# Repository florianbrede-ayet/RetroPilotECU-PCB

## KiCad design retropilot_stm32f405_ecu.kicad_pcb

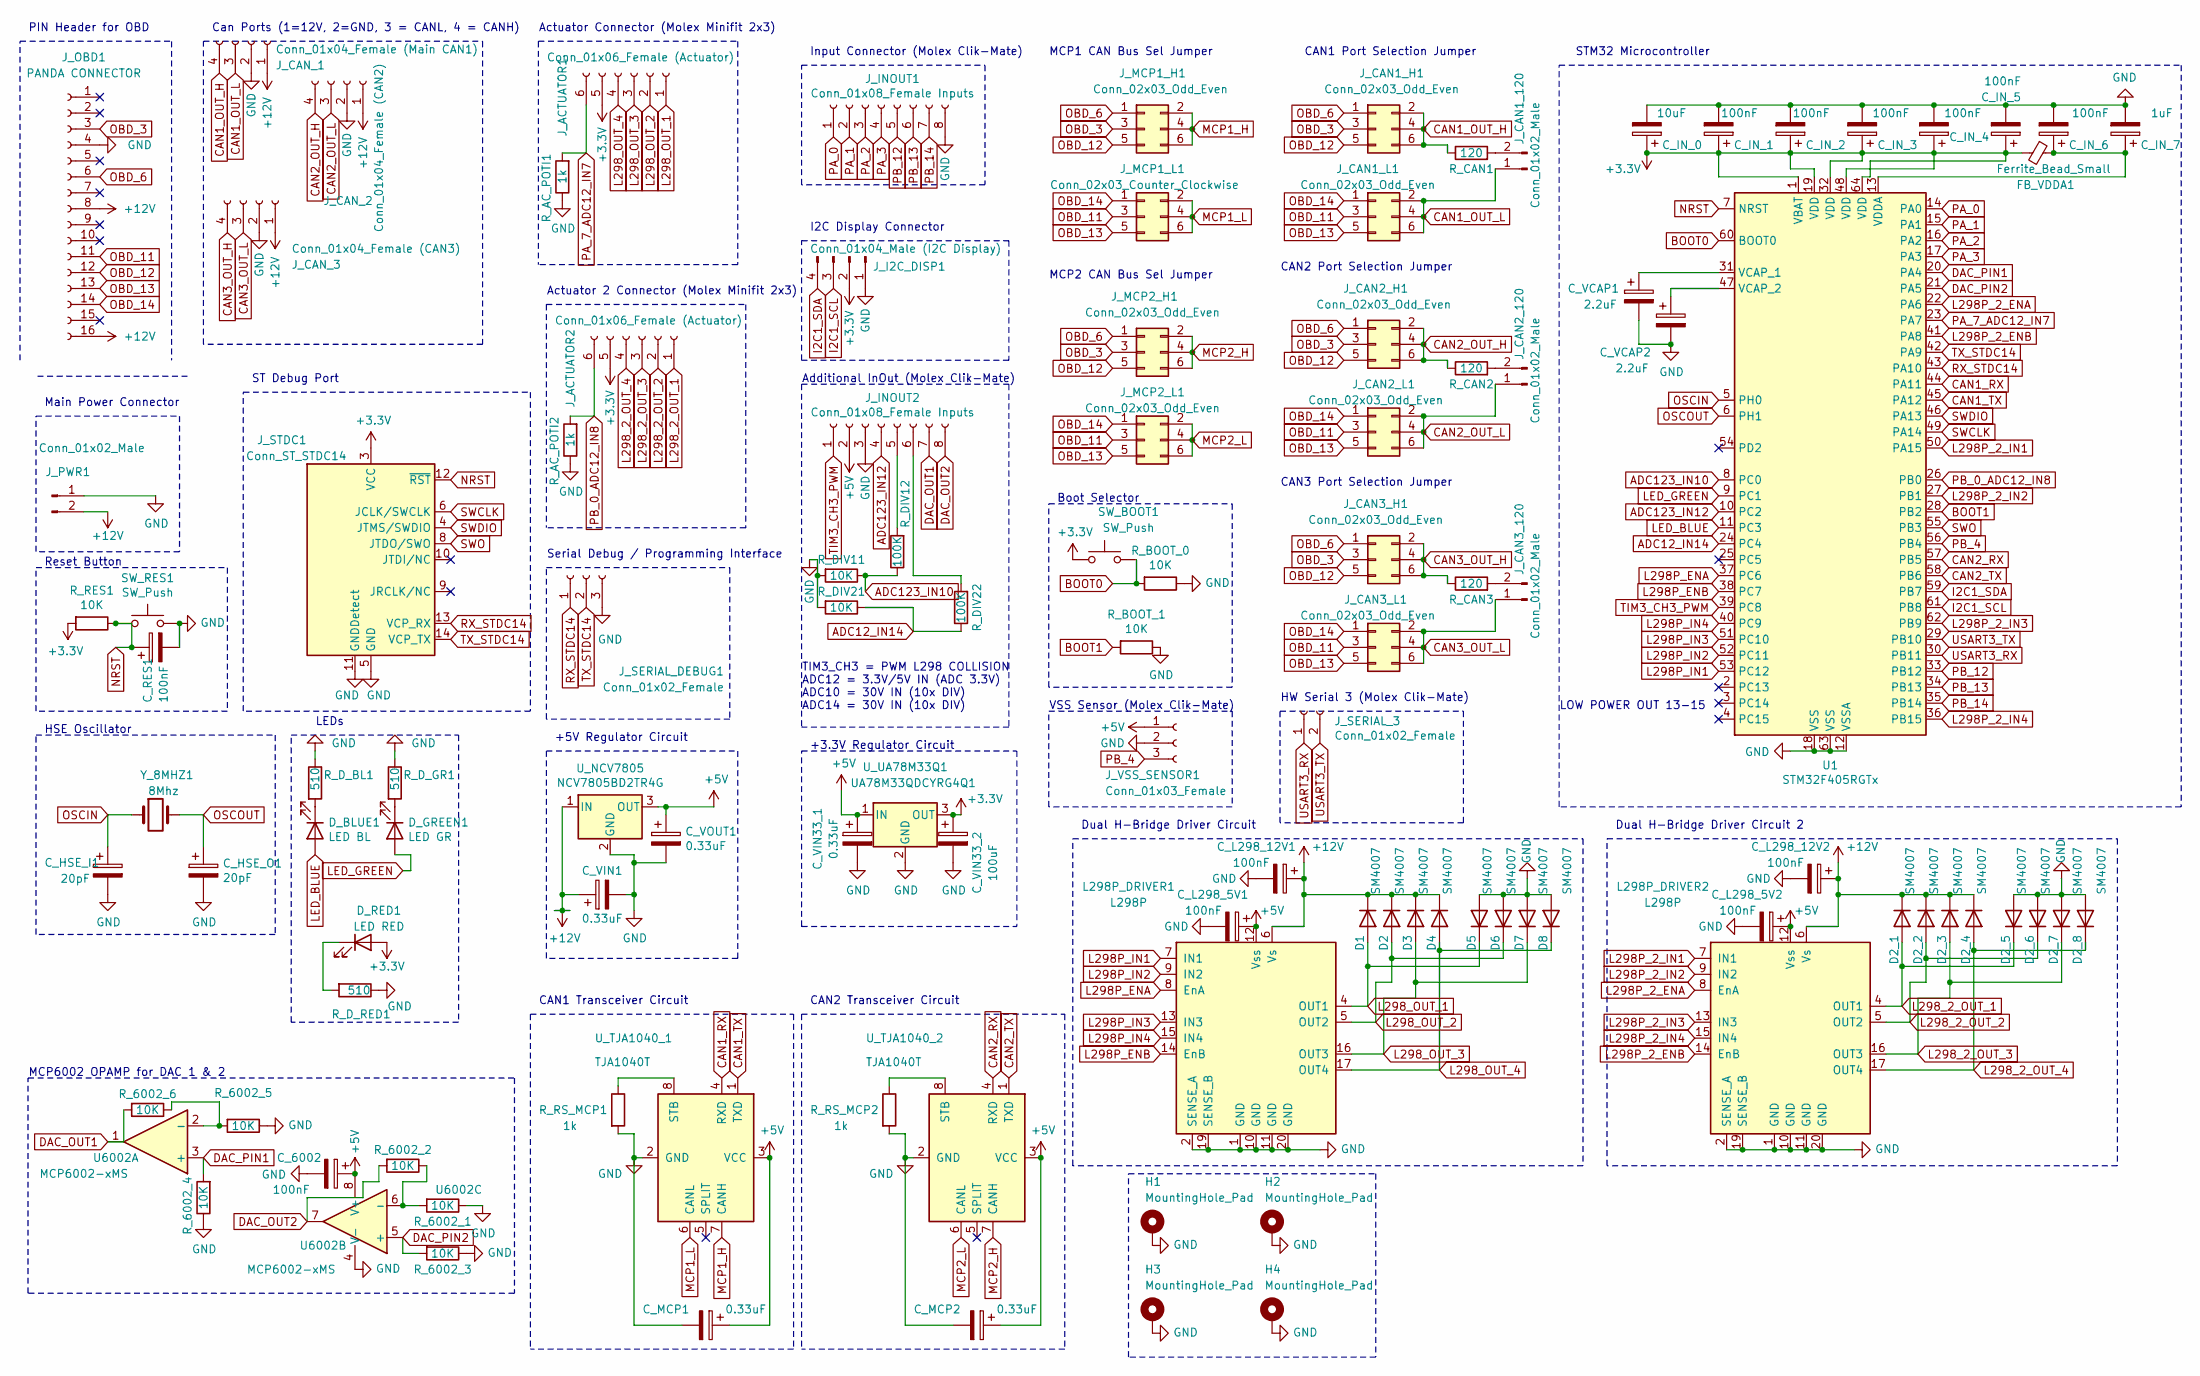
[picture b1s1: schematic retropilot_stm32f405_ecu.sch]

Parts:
C_6002: 100nF; C_0402_1005Metric
C_HSE_I1: 20pF; C_0603_1608Metric
C_HSE_O1: 20pF; C_0603_1608Metric
C_IN_0: 10uF; CP_EIA-3216-18_Kemet-A
C_IN_1, C_IN_2, C_IN_3, C_IN_4, C_IN_5, C_IN_6: 100nF; C_0402_1005Metric
C_IN_7: 1uF; C_1206_3216Metric
C_L298_5V1, C_L298_5V2, C_L298_12V1, C_L298_12V2: 100nF; C_0402_1005Metric
C_MCP1, C_MCP2: 0.33uF; C_0805_2012Metric
C_RES1: 100nF; C_0402_1005Metric
C_VCAP1, C_VCAP2: 2.2uF; C_1206_3216Metric
C_VIN1, C_VIN33_1: 0.33uF; C_0805_2012Metric
C_VIN33_2: 100uF; CP_EIA-3528-15_AVX-H
C_VOUT1: 0.33uF; C_0805_2012Metric
D1, D2, D2_1, D2_2, D2_3, D2_4, D2_5, D2_6, D2_7, D2_8, D3, D4, D5, D6, D7, D8: SM4007; D_SOD-123F
D_BLUE1: LED BL; LED_0603_1608Metric
D_GREEN1: LED GR; LED_0603_1608Metric
D_RED1: LED RED; LED_0603_1608Metric
FB_VDDA1: Ferrite_Bead_Small; R_0805_2012Metric
H1, H2, H3, H4: MountingHole_Pad; MountingHole_3.2mm_M3_DIN965_Pad
J_ACTUATOR1, J_ACTUATOR2: Conn_01x06_Female (Actuator); Molex_Mini-Fit_Jr_5569-06A2_2x03_P4.20mm_Horizontal
J_CAN1_120, J_CAN2_120, J_CAN3_120: Conn_01x02_Male; PinHeader_1x02_P1.27mm_Vertical
J_CAN1_H1, J_CAN1_L1, J_CAN2_H1, J_CAN2_L1, J_CAN3_H1, J_CAN3_L1: Conn_02x03_Odd_Even; PinHeader_2x03_P1.27mm_Vertical
J_CAN_1: Conn_01x04_Female (Main CAN1); Molex_Mini-Fit_Jr_5569-04A2_2x02_P4.20mm_Horizontal
J_CAN_2: Conn_01x04_Female (CAN2); Molex_Mini-Fit_Jr_5569-04A2_2x02_P4.20mm_Horizontal
J_CAN_3: Conn_01x04_Female (CAN3); Molex_Mini-Fit_Jr_5569-04A2_2x02_P4.20mm_Horizontal
J_I2C_DISP1: Conn_01x04_Male (I2C Display); PinSocket_1x04_P2.54mm_Vertical
J_INOUT1, J_INOUT2: Conn_01x08_Female Inputs; Molex_CLIK-Mate_502386-0870_1x08-1MP_P1.25mm_Horizontal
J_MCP1_H1, J_MCP2_H1, J_MCP2_L1: Conn_02x03_Odd_Even; PinHeader_2x03_P1.27mm_Vertical
J_MCP1_L1: Conn_02x03_Counter_Clockwise; PinHeader_2x03_P1.27mm_Vertical
J_OBD1: PANDA CONNECTOR; C-OBD-II-16M-E-N-12V
J_PWR1: Conn_01x02_Male; Molex_Mini-Fit_Jr_5569-02A2_2x01_P4.20mm_Horizontal
J_SERIAL_3: Conn_01x02_Female; Molex_CLIK-Mate_502386-0270_1x02-1MP_P1.25mm_Horizontal
J_SERIAL_DEBUG1: Conn_01x02_Female; PinSocket_1x03_P2.54mm_Horizontal
J_STDC1: Conn_ST_STDC14; PinHeader_2x07_P2.54mm_Vertical
J_VSS_SENSOR1: Conn_01x03_Female; Molex_CLIK-Mate_502386-0370_1x03-1MP_P1.25mm_Horizontal
L298P_DRIVER1, L298P_DRIVER2: L298P; HSOP-20-1EP_11.0x15.9mm_P1.27mm_SlugDown
R_6002_1, R_6002_2, R_6002_3, R_6002_4, R_6002_5, R_6002_6: 10K; R_0603_1608Metric
R_AC_POTI1, R_AC_POTI2: 1k; R_0603_1608Metric
R_BOOT_0, R_BOOT_1: 10K; R_0603_1608Metric
R_CAN1, R_CAN2, R_CAN3: 120; R_0603_1608Metric
R_DIV11, R_DIV21: 10K; R_0603_1608Metric
R_DIV12, R_DIV22: 100K; R_0603_1608Metric
R_D_BL1: 510; R_0603_1608Metric
R_D_GR1: 510; R_0603_1608Metric
R_D_RED1: 510; R_0603_1608Metric
R_RES1: 10K; R_0603_1608Metric
R_RS_MCP1, R_RS_MCP2: 1k; R_0603_1608Metric
SW_BOOT1: SW_Push; SW_Push_1P1T_NO_CK_KSC6xxJ
SW_RES1: SW_Push; SW_Push_1P1T_NO_CK_KSC6xxJ
U1: STM32F405RGTx; LQFP-64_10x10mm_P0.5mm
U6002: MCP6002-xMS; SOIC-8_3.9x4.9mm_P1.27mm
U_NCV7805: NCV7805BD2TR4G; TO-263-3_TabPin2
U_TJA1040_1, U_TJA1040_2: TJA1040T; SOIC-8_3.9x4.9mm_P1.27mm
U_UA78M33Q1: UA78M33QDCYRG4Q1; SOT-223-3_TabPin2
Y_8MHZ1: 8Mhz; Crystal_SMD_5032-2Pin_5.0x3.2mm

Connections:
+3V3: C_IN_0.1, C_IN_1.1, C_IN_2.1, C_IN_3.1, C_IN_4.1, C_IN_5.1, C_VIN33_2.1, D_RED1.2 (A), FB_VDDA1.2, J_ACTUATOR1.5, J_ACTUATOR2.5, J_I2C_DISP1.2, J_STDC1.3 (VCC), R_RES1.2, SW_BOOT1.1, U1.1 (VBAT), U1.19 (VDD), U1.32 (VDD), U1.48 (VDD), U1.64 (VDD), U_UA78M33Q1.3 (OUT)
+5V: C_6002.1, C_L298_5V1.1, C_L298_5V2.1, C_MCP1.1, C_MCP2.1, C_VIN33_1.1, C_VOUT1.1, J_INOUT2.2, J_VSS_SENSOR1.1, L298P_DRIVER1.12 (Vss), L298P_DRIVER2.12 (Vss), U6002.8 (V+), U_NCV7805.3 (OUT), U_TJA1040_1.3 (VCC), U_TJA1040_2.3 (VCC), U_UA78M33Q1.1 (IN)
+12V: C_L298_12V1.1, C_L298_12V2.1, C_VIN1.1, D1.1 (K), D2.1 (K), D2_1.1 (K), D2_2.1 (K), D2_3.1 (K), D2_4.1 (K), D3.1 (K), D4.1 (K), J_CAN_1.1, J_CAN_2.1, J_CAN_3.1, J_OBD1.8, J_OBD1.16, J_PWR1.2, L298P_DRIVER1.6 (Vs), L298P_DRIVER2.6 (Vs), U_NCV7805.1 (IN)
ADC12_IN14: R_DIV21.1, R_DIV22.1, U1.24 (PC4)
ADC123_IN10: R_DIV11.1, R_DIV12.1, U1.8 (PC0)
ADC123_IN12: J_INOUT2.4, U1.10 (PC2)
BOOT0: R_BOOT_0.2, SW_BOOT1.2, U1.60 (BOOT0)
BOOT1: R_BOOT_1.2, U1.28 (PB2)
CAN1_OUT_H: J_CAN1_H1.2, J_CAN1_H1.4, J_CAN1_H1.6, J_CAN_1.4, R_CAN1.1
CAN1_OUT_L: J_CAN1_120.1, J_CAN1_L1.2, J_CAN1_L1.4, J_CAN1_L1.6, J_CAN_1.3
CAN1_RX: U1.44 (PA11), U_TJA1040_1.4 (RXD)
CAN1_TX: U1.45 (PA12), U_TJA1040_1.1 (TXD)
CAN2_OUT_H: J_CAN2_H1.2, J_CAN2_H1.4, J_CAN2_H1.6, J_CAN_2.4, R_CAN2.1
CAN2_OUT_L: J_CAN2_120.1, J_CAN2_L1.2, J_CAN2_L1.4, J_CAN2_L1.6, J_CAN_2.3
CAN2_RX: U1.57 (PB5), U_TJA1040_2.4 (RXD)
CAN2_TX: U1.58 (PB6), U_TJA1040_2.1 (TXD)
CAN3_OUT_H: J_CAN3_H1.2, J_CAN3_H1.4, J_CAN3_H1.6, J_CAN_3.4, R_CAN3.1
CAN3_OUT_L: J_CAN3_120.1, J_CAN3_L1.2, J_CAN3_L1.4, J_CAN3_L1.6, J_CAN_3.3
DAC_OUT1: J_INOUT2.7, R_6002_6.2, U6002.1
DAC_OUT2: J_INOUT2.8, R_6002_2.2, U6002.7
DAC_PIN1: R_6002_4.2, U1.20 (PA4), U6002.3 (+)
DAC_PIN2: R_6002_3.2, U1.21 (PA5), U6002.5 (+)
GND: C_6002.2, C_HSE_I1.2, C_HSE_O1.2, C_IN_0.2, C_IN_1.2, C_IN_2.2, C_IN_3.2, C_IN_4.2, C_IN_5.2, C_IN_6.2, C_IN_7.2, C_L298_5V1.2, C_L298_5V2.2, C_L298_12V1.2, C_L298_12V2.2, C_MCP1.2, C_MCP2.2, C_RES1.2, C_VCAP1.2, C_VCAP2.2, C_VIN1.2, C_VIN33_1.2, C_VIN33_2.2, C_VOUT1.2, D2_5.2 (A), D2_6.2 (A), D2_7.2 (A), D2_8.2 (A), D5.2 (A), D6.2 (A), D7.2 (A), D8.2 (A), H1.1, H2.1, H3.1, H4.1, J_CAN_1.2, J_CAN_2.2, J_CAN_3.2, J_I2C_DISP1.1, J_INOUT1.8, J_INOUT2.3, J_OBD1.4, J_PWR1.1, J_SERIAL_DEBUG1.3, J_STDC1.5 (GND), J_STDC1.7 (GND), J_STDC1.11 (GNDDetect), J_VSS_SENSOR1.2, L298P_DRIVER1.1 (GND), L298P_DRIVER1.2 (SENSE_A), L298P_DRIVER1.10 (GND), L298P_DRIVER1.11 (GND), L298P_DRIVER1.19 (SENSE_B), L298P_DRIVER1.20 (GND), L298P_DRIVER2.1 (GND), L298P_DRIVER2.2 (SENSE_A), L298P_DRIVER2.10 (GND), L298P_DRIVER2.11 (GND), L298P_DRIVER2.19 (SENSE_B), L298P_DRIVER2.20 (GND), R_6002_1.1, R_6002_3.1, R_6002_4.1, R_6002_5.1, R_AC_POTI1.1, R_AC_POTI2.1, R_BOOT_0.1, R_BOOT_1.1, R_DIV11.2, R_DIV21.2, R_D_BL1.1, R_D_GR1.1, R_D_RED1.1, R_RS_MCP1.2, R_RS_MCP2.2, SW_RES1.2, U1.12 (VSSA), U1.18 (VSS), U1.63 (VSS), U6002.4 (V-), U_NCV7805.2 (GND), U_TJA1040_1.2 (GND), U_TJA1040_2.2 (GND), U_UA78M33Q1.2 (GND)
I2C1_SCL: J_I2C_DISP1.3, U1.61 (PB8)
I2C1_SDA: J_I2C_DISP1.4, U1.59 (PB7)
L298P_2_ENA: L298P_DRIVER2.8 (EnA), U1.22 (PA6)
L298P_2_ENB: L298P_DRIVER2.14 (EnB), U1.41 (PA8)
L298P_2_IN1: L298P_DRIVER2.7 (IN1), U1.50 (PA15)
L298P_2_IN2: L298P_DRIVER2.9 (IN2), U1.27 (PB1)
L298P_2_IN3: L298P_DRIVER2.13 (IN3), U1.62 (PB9)
L298P_2_IN4: L298P_DRIVER2.15 (IN4), U1.36 (PB15)
L298P_ENA: L298P_DRIVER1.8 (EnA), U1.37 (PC6)
L298P_ENB: L298P_DRIVER1.14 (EnB), U1.38 (PC7)
L298P_IN1: L298P_DRIVER1.7 (IN1), U1.53 (PC12)
L298P_IN2: L298P_DRIVER1.9 (IN2), U1.52 (PC11)
L298P_IN3: L298P_DRIVER1.13 (IN3), U1.51 (PC10)
L298P_IN4: L298P_DRIVER1.15 (IN4), U1.40 (PC9)
L298_2_OUT_1: D2_1.2 (A), D2_5.1 (K), J_ACTUATOR2.1, L298P_DRIVER2.4 (OUT1)
L298_2_OUT_2: D2_2.2 (A), D2_6.1 (K), J_ACTUATOR2.2, L298P_DRIVER2.5 (OUT2)
L298_2_OUT_3: D2_3.2 (A), D2_7.1 (K), J_ACTUATOR2.3, L298P_DRIVER2.16 (OUT3)
L298_2_OUT_4: D2_4.2 (A), D2_8.1 (K), J_ACTUATOR2.4, L298P_DRIVER2.17 (OUT4)
L298_OUT_1: D1.2 (A), D5.1 (K), J_ACTUATOR1.1, L298P_DRIVER1.4 (OUT1)
L298_OUT_2: D2.2 (A), D6.1 (K), J_ACTUATOR1.2, L298P_DRIVER1.5 (OUT2)
L298_OUT_3: D3.2 (A), D7.1 (K), J_ACTUATOR1.3, L298P_DRIVER1.16 (OUT3)
L298_OUT_4: D4.2 (A), D8.1 (K), J_ACTUATOR1.4, L298P_DRIVER1.17 (OUT4)
LED_BLUE: D_BLUE1.2 (A), U1.11 (PC3)
LED_GREEN: D_GREEN1.2 (A), U1.9 (PC1)
MCP1_H: J_MCP1_H1.2, J_MCP1_H1.4, J_MCP1_H1.6, U_TJA1040_1.7 (CANH)
MCP1_L: J_MCP1_L1.2, J_MCP1_L1.4, J_MCP1_L1.6, U_TJA1040_1.6 (CANL)
MCP2_H: J_MCP2_H1.2, J_MCP2_H1.4, J_MCP2_H1.6, U_TJA1040_2.7 (CANH)
MCP2_L: J_MCP2_L1.2, J_MCP2_L1.4, J_MCP2_L1.6, U_TJA1040_2.6 (CANL)
NRST: C_RES1.1, J_STDC1.12 (~RST), R_RES1.1, SW_RES1.1, U1.7 (NRST)
unnamed: C_IN_6.1, C_IN_7.1, FB_VDDA1.1, U1.13 (VDDA)
unnamed: C_VCAP1.1, U1.31 (VCAP_1)
unnamed: C_VCAP2.1, U1.47 (VCAP_2)
unnamed: D_BLUE1.1 (K), R_D_BL1.2
unnamed: D_GREEN1.1 (K), R_D_GR1.2
unnamed: D_RED1.1 (K), R_D_RED1.2
unnamed: J_CAN1_120.2, R_CAN1.2
unnamed: J_CAN2_120.2, R_CAN2.2
unnamed: J_CAN3_120.2, R_CAN3.2
unnamed: J_INOUT2.5, R_DIV12.2
unnamed: J_INOUT2.6, R_DIV22.2
unnamed: R_6002_1.2, R_6002_2.1, U6002.6 (-)
unnamed: R_6002_5.2, R_6002_6.1, U6002.2 (-)
unnamed: R_RS_MCP1.1, U_TJA1040_1.8 (STB)
unnamed: R_RS_MCP2.1, U_TJA1040_2.8 (STB)
OBD_3: J_CAN1_H1.3, J_CAN2_H1.3, J_CAN3_H1.3, J_MCP1_H1.3, J_MCP2_H1.3, J_OBD1.3
OBD_6: J_CAN1_H1.1, J_CAN2_H1.1, J_CAN3_H1.1, J_MCP1_H1.1, J_MCP2_H1.1, J_OBD1.6
OBD_11: J_CAN1_L1.3, J_CAN2_L1.3, J_CAN3_L1.3, J_MCP1_L1.3, J_MCP2_L1.3, J_OBD1.11
OBD_12: J_CAN1_H1.5, J_CAN2_H1.5, J_CAN3_H1.5, J_MCP1_H1.5, J_MCP2_H1.5, J_OBD1.12
OBD_13: J_CAN1_L1.5, J_CAN2_L1.5, J_CAN3_L1.5, J_MCP1_L1.5, J_MCP2_L1.5, J_OBD1.13
OBD_14: J_CAN1_L1.1, J_CAN2_L1.1, J_CAN3_L1.1, J_MCP1_L1.1, J_MCP2_L1.1, J_OBD1.14
OSCIN: C_HSE_I1.1, U1.5 (PH0), Y_8MHZ1.1
OSCOUT: C_HSE_O1.1, U1.6 (PH1), Y_8MHZ1.2
PA_0: J_INOUT1.1, U1.14 (PA0)
PA_1: J_INOUT1.2, U1.15 (PA1)
PA_2: J_INOUT1.3, U1.16 (PA2)
PA_3: J_INOUT1.4, U1.17 (PA3)
PA_7_ADC12_IN7: J_ACTUATOR1.6, R_AC_POTI1.2, U1.23 (PA7)
PB_0_ADC12_IN8: J_ACTUATOR2.6, R_AC_POTI2.2, U1.26 (PB0)
PB_4: J_VSS_SENSOR1.3, U1.56 (PB4)
PB_12: J_INOUT1.5, U1.33 (PB12)
PB_13: J_INOUT1.6, U1.34 (PB13)
PB_14: J_INOUT1.7, U1.35 (PB14)
RX_STDC14: J_SERIAL_DEBUG1.1, J_STDC1.13 (VCP_RX), U1.43 (PA10)
SWCLK: J_STDC1.6 (JCLK/SWCLK), U1.49 (PA14)
SWDIO: J_STDC1.4 (JTMS/SWDIO), U1.46 (PA13)
SWO: J_STDC1.8 (JTDO/SWO), U1.55 (PB3)
TIM3_CH3_PWM: J_INOUT2.1, U1.39 (PC8)
TX_STDC14: J_SERIAL_DEBUG1.2, J_STDC1.14 (VCP_TX), U1.42 (PA9)
USART3_RX: J_SERIAL_3.1, U1.30 (PB11)
USART3_TX: J_SERIAL_3.2, U1.29 (PB10)

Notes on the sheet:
Dual H-Bridge Driver Circuit
CAN1 Transceiver Circuit
+5V Regulator Circuit
+3.3V Regulator Circuit
HSE Oscillator
Reset Button
Boot Selector
Main Power Connector
LEDs
PIN Header for OBD
STM32 Microcontroller
Can Ports (1=12V, 2=GND, 3 = CANL, 4 = CANH)
Actuator Connector (Molex Minifit 2x3)
Input Connector (Molex Clik-Mate)
I2C Display Connector
Serial Debug / Programming Interface
HW Serial 3 (Molex Clik-Mate)
Additional InOut (Molex Clik-Mate)
TIM3_CH3 = PWM L298 COLLISION ADC12 = 3.3V/5V IN (ADC 3.3V) ADC10 = 30V IN (10x DIV) ADC14 = 30V IN (10x DIV)
MCP1 CAN Bus Sel Jumper
CAN1 Port Selection Jumper
CAN2 Port Selection Jumper
CAN2 Transceiver Circuit
MCP2 CAN Bus Sel Jumper
CAN3 Port Selection Jumper
ST Debug Port
LOW POWER OUT 13-15
VSS Sensor (Molex Clik-Mate)
MCP6002 OPAMP for DAC 1 & 2
Dual H-Bridge Driver Circuit 2
Actuator 2 Connector (Molex Minifit 2x3)

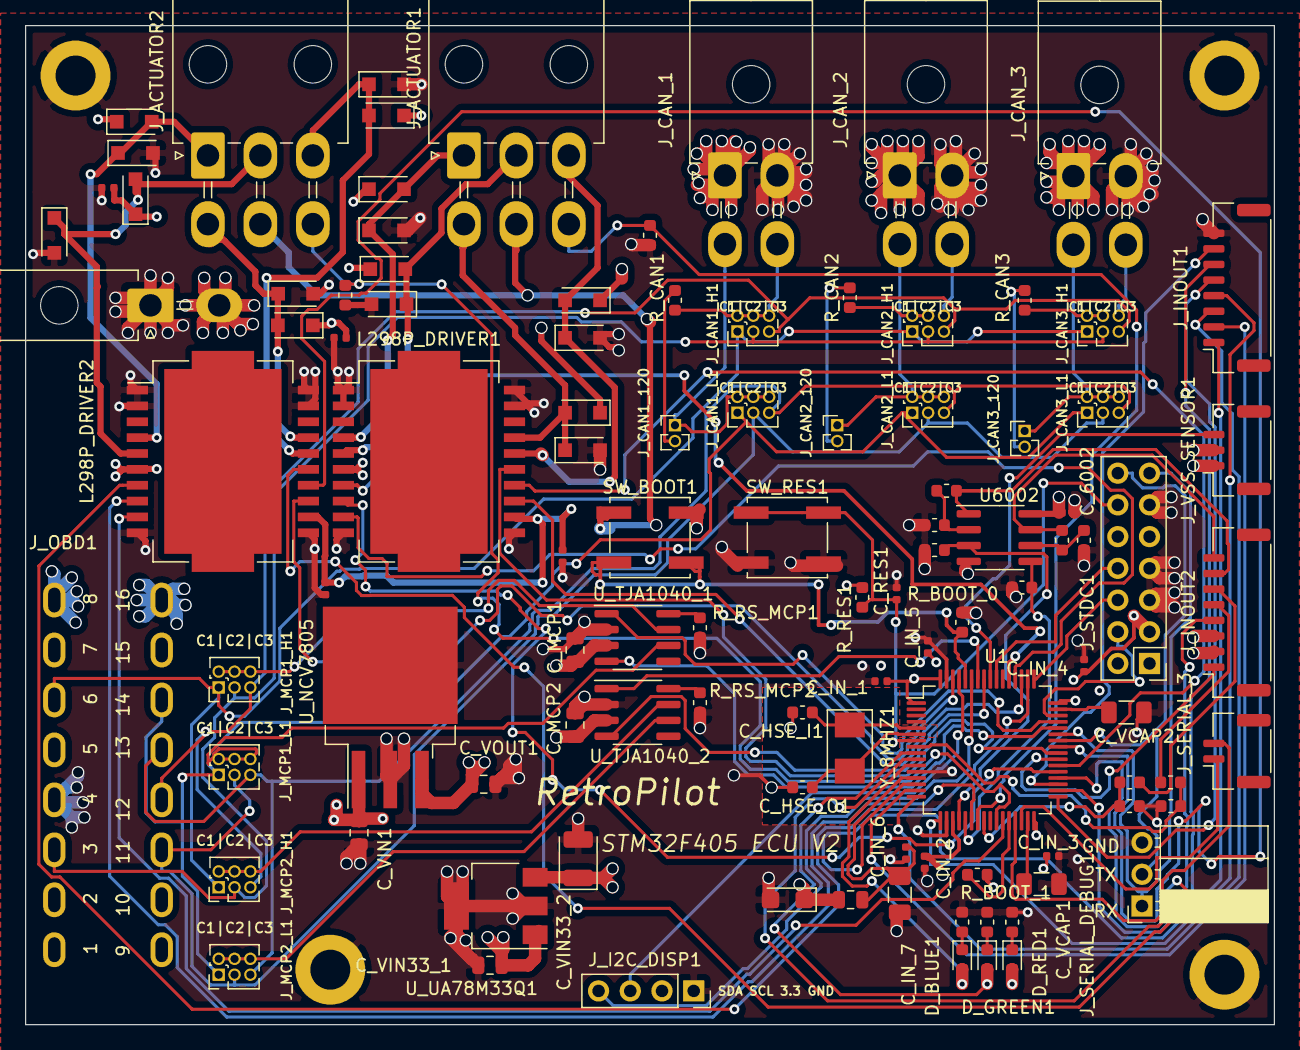
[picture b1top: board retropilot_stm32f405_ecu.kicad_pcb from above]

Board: 4 copper layers, 100.0 x 80.0 mm, 109 parts (0 on the bottom side), 93 nets.

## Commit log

2020-08-26 TODO: initial commit
2020-08-26 TODO: updated complete BOM
